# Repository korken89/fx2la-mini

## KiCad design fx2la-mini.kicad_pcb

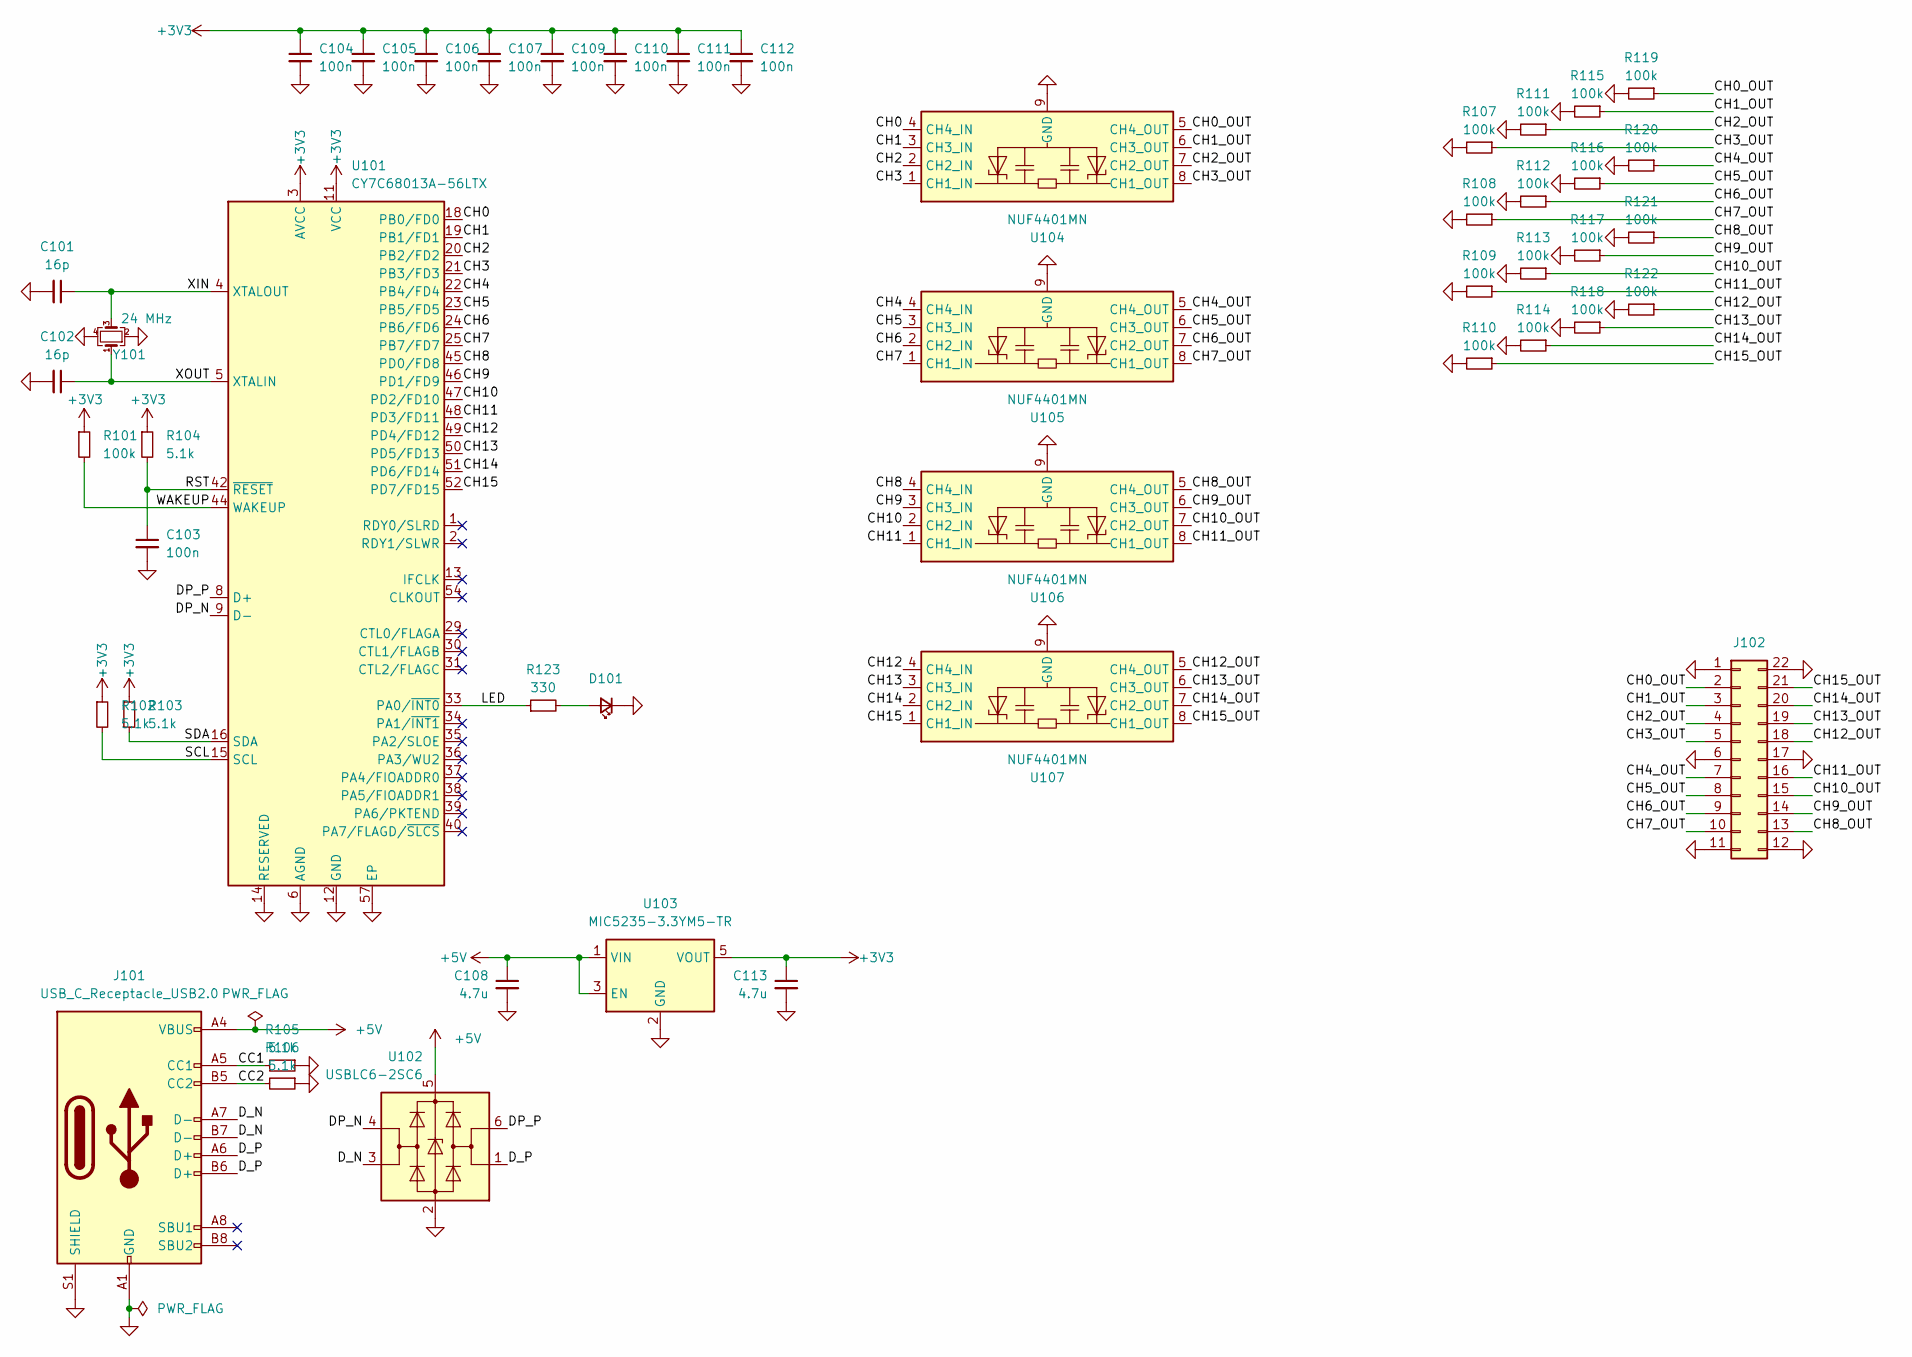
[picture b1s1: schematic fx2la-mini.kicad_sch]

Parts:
C101, C102: 16p; C_0402; LCSC C396888
C103, C104, C105, C106, C107, C109, C110, C111, C112: 100n; C_0402; LCSC C2874742
C108, C113: 4.7u; C_0402; LCSC C368809
D101: LED_Small; LED_0603_1608Metric; LCSC C85323
J101: USB_C_Receptacle_USB2.0; USB_C_Receptacle_USB4105; LCSC C165948
J102: Conn_02x11_Counter_Clockwise; 2x11_2.54mm_side; LCSC C725883
R101, R107, R108, R109, R110, R111, R112, R113, R114, R115, R116, R117, R118, R119, R120, R121, R122: 100k; R_0402; LCSC C60491
R102, R103, R104, R105, R106: 5.1k; R_0402; LCSC C203181
R123: 330; R_0402; LCSC C168264
U101: CY7C68013A-56LTX; QFN-56-1EP_8x8mm_P0.5mm_EP4.5x5.2mm; LCSC C14912
U102: USBLC6-2SC6; SOT-23-6; LCSC C7519
U103: MIC5235-3.3YM5-TR; SOT-23-5; LCSC C89886
U104, U105, U106, U107: NUF4401MN; DFN-8-1EP_2x2mm_P0.5mm_EP0.7x1.3mm; LCSC C479731
Y101: 24 MHz; Crystal_4Pin_2.0x1.6mm; LCSC C2689430

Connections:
+3V3: C104.1, C105.1, C106.1, C107.1, C109.1, C110.1, C111.1, C112.1, C113.1, R101.1, R102.1, R103.1, R104.1, U101.3 (AVCC), U101.7 (AVCC), U101.11 (VCC), U101.17 (VCC), U101.27 (VCC), U101.32 (VCC), U101.43 (VCC), U101.55 (VCC), U103.5 (VOUT)
+5V: C108.1, J101.A4 (VBUS), J101.A9 (VBUS), J101.B4 (VBUS), J101.B9 (VBUS), U102.5 (VBUS), U103.1 (VIN), U103.3 (EN)
/CC1: J101.A5 (CC1), R105.2
/CC2: J101.B5 (CC2), R106.2
/CH0: U101.18 (PB0/FD0), U104.4 (CH4_IN)
/CH0_OUT: J102.2, R119.1, U104.5 (CH4_OUT)
/CH1: U101.19 (PB1/FD1), U104.3 (CH3_IN)
/CH1_OUT: J102.3, R115.1, U104.6 (CH3_OUT)
/CH2: U101.20 (PB2/FD2), U104.2 (CH2_IN)
/CH2_OUT: J102.4, R111.1, U104.7 (CH2_OUT)
/CH3: U101.21 (PB3/FD3), U104.1 (CH1_IN)
/CH3_OUT: J102.5, R107.1, U104.8 (CH1_OUT)
/CH4: U101.22 (PB4/FD4), U105.4 (CH4_IN)
/CH4_OUT: J102.7, R120.1, U105.5 (CH4_OUT)
/CH5: U101.23 (PB5/FD5), U105.3 (CH3_IN)
/CH5_OUT: J102.8, R116.1, U105.6 (CH3_OUT)
/CH6: U101.24 (PB6/FD6), U105.2 (CH2_IN)
/CH6_OUT: J102.9, R112.1, U105.7 (CH2_OUT)
/CH7: U101.25 (PB7/FD7), U105.1 (CH1_IN)
/CH7_OUT: J102.10, R108.1, U105.8 (CH1_OUT)
/CH8: U101.45 (PD0/FD8), U106.4 (CH4_IN)
/CH8_OUT: J102.13, R121.1, U106.5 (CH4_OUT)
/CH9: U101.46 (PD1/FD9), U106.3 (CH3_IN)
/CH9_OUT: J102.14, R117.1, U106.6 (CH3_OUT)
/CH10: U101.47 (PD2/FD10), U106.2 (CH2_IN)
/CH10_OUT: J102.15, R113.1, U106.7 (CH2_OUT)
/CH11: U101.48 (PD3/FD11), U106.1 (CH1_IN)
/CH11_OUT: J102.16, R109.1, U106.8 (CH1_OUT)
/CH12: U101.49 (PD4/FD12), U107.4 (CH4_IN)
/CH12_OUT: J102.18, R122.1, U107.5 (CH4_OUT)
/CH13: U101.50 (PD5/FD13), U107.3 (CH3_IN)
/CH13_OUT: J102.19, R118.1, U107.6 (CH3_OUT)
/CH14: U101.51 (PD6/FD14), U107.2 (CH2_IN)
/CH14_OUT: J102.20, R114.1, U107.7 (CH2_OUT)
/CH15: U101.52 (PD7/FD15), U107.1 (CH1_IN)
/CH15_OUT: J102.21, R110.1, U107.8 (CH1_OUT)
/DP_N: U101.9 (D-), U102.4 (I/O2)
/DP_P: U101.8 (D+), U102.6 (I/O1)
/D_N: J101.A7 (D-), J101.B7 (D-), U102.3 (I/O2)
/D_P: J101.A6 (D+), J101.B6 (D+), U102.1 (I/O1)
/LED: R123.1, U101.33 (PA0/~INT0)
/RST: C103.1, R104.2, U101.42 (~RESET)
/SCL: R102.2, U101.15 (SCL)
/SDA: R103.2, U101.16 (SDA)
/WAKEUP: R101.2, U101.44 (WAKEUP)
/XIN: C101.1, U101.4 (XTALOUT), Y101.3
/XOUT: C102.1, U101.5 (XTALIN), Y101.1
GND: C101.2, C102.2, C103.2, C104.2, C105.2, C106.2, C107.2, C108.2, C109.2, C110.2, C111.2, C112.2, C113.2, D101.1 (K), J101.A1 (GND), J101.A12 (GND), J101.B1 (GND), J101.B12 (GND), J101.S1 (SHIELD), J102.1, J102.6, J102.11, J102.12, J102.17, J102.22, R105.1, R106.1, R107.2, R108.2, R109.2, R110.2, R111.2, R112.2, R113.2, R114.2, R115.2, R116.2, R117.2, R118.2, R119.2, R120.2, R121.2, R122.2, U101.6 (AGND), U101.10 (AGND), U101.12 (GND), U101.14 (RESERVED), U101.26 (GND), U101.28 (GND), U101.41 (GND), U101.53 (GND), U101.56 (GND), U101.57 (EP), U102.2 (GND), U103.2 (GND), U104.9 (GND), U105.9 (GND), U106.9 (GND), U107.9 (GND), Y101.2, Y101.4
unnamed: D101.2 (A), R123.2

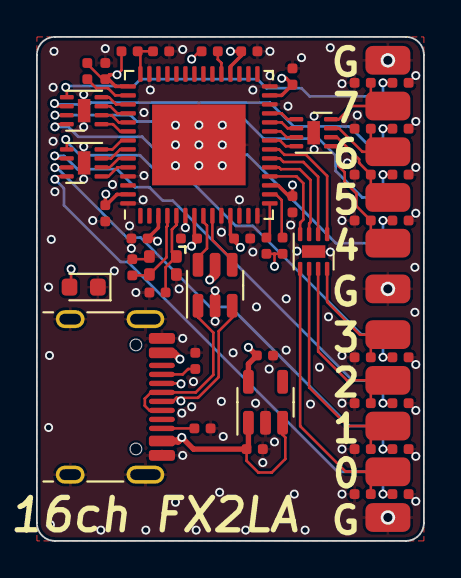
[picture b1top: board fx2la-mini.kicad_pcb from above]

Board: 4 copper layers, 21.5 x 28.0 mm, 47 parts (0 on the bottom side), 49 nets.

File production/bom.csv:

Designator,Footprint,Quantity,Value,LCSC Part #
"C101, C102",C_0402,2,16p,C396888
"C103, C104, C105, C106, C107, C109, C110, C111, C112",C_0402,9,100n,C2874742
"C108, C113",C_0402,2,4.7u,C368809
D101,0603,1,LED_Small,C85323
J101,USB_C_Receptacle_USB4105,1,USB_C_Receptacle_USB2.0,C165948
J102,2x11_2.54mm_side,1,Conn_02x11_Counter_Clockwise,C725883
"R101, R107, R108, R109, R110, R111, R112, R113, R114, R115, R116, R117, R118, R119, R120, R121, R122",R_0402,17,100k,C60491
"R102, R103, R104, R105, R106",R_0402,5,5.1k,C203181
R123,R_0402,1,330,C168264
U101,QFN-56-1EP_8x8mm_P0.5mm_EP4.5x5.2mm,1,CY7C68013A-56LTX,C14912
U102,SOT-23-6,1,USBLC6-2SC6,C7519
U103,SOT-23-5,1,MIC5235-3.3YM5-TR,C89886
"U104, U105, U106, U107",DFN-8-1EP_2x2mm_P0.5mm_EP0.7x1.3mm,4,NUF4401MN,C479731
Y101,Crystal_4Pin_2.0x1.6mm,1,24 MHz,C2689430

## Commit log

2022-12-12 Project init
2023-08-23 Save
2023-08-23 Hijack project to 16 channels
2023-08-23 Layout complete
2023-08-26 Add LED to PA1, update some part numbers that were out of stock now
